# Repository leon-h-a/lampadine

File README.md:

### Connection between Arduino and PCB header
    ARD_13  -> 1
    ARD_12  -> 2
    ARD_11  -> 3
    ARD_10  -> 4
    ARD_GND -> 5

### Settings for programming via Arduino (platformio)
1. Install platformio on Windows
2. Init project ```pio project init --board attiny85``` ($ pio boards)
3. Install dependency ```pio lib install ADCTouch```
4. Setup Platformio to flash via Arduino (platformio.ini)

        [env:attiny85]
        platform = atmelavr
        board = attiny85
        framework = arduino
        upload_protocol = stk500v1
        lib_deps = martin2250/ADCTouch@^1.0.4
        upload_flags =
                -P$UPLOAD_PORT
                -b$UPLOAD_SPEED
        upload_port = COM7
        upload_speed = 19200

5. Flash with ```pio run --target upload```

### In case of avrdude verification error, mismatch byte

Remember to power PCB via USB-C before uploading.

### Timing issues

Define 'board_build.f_cpu' flag in platformio.ini conf file

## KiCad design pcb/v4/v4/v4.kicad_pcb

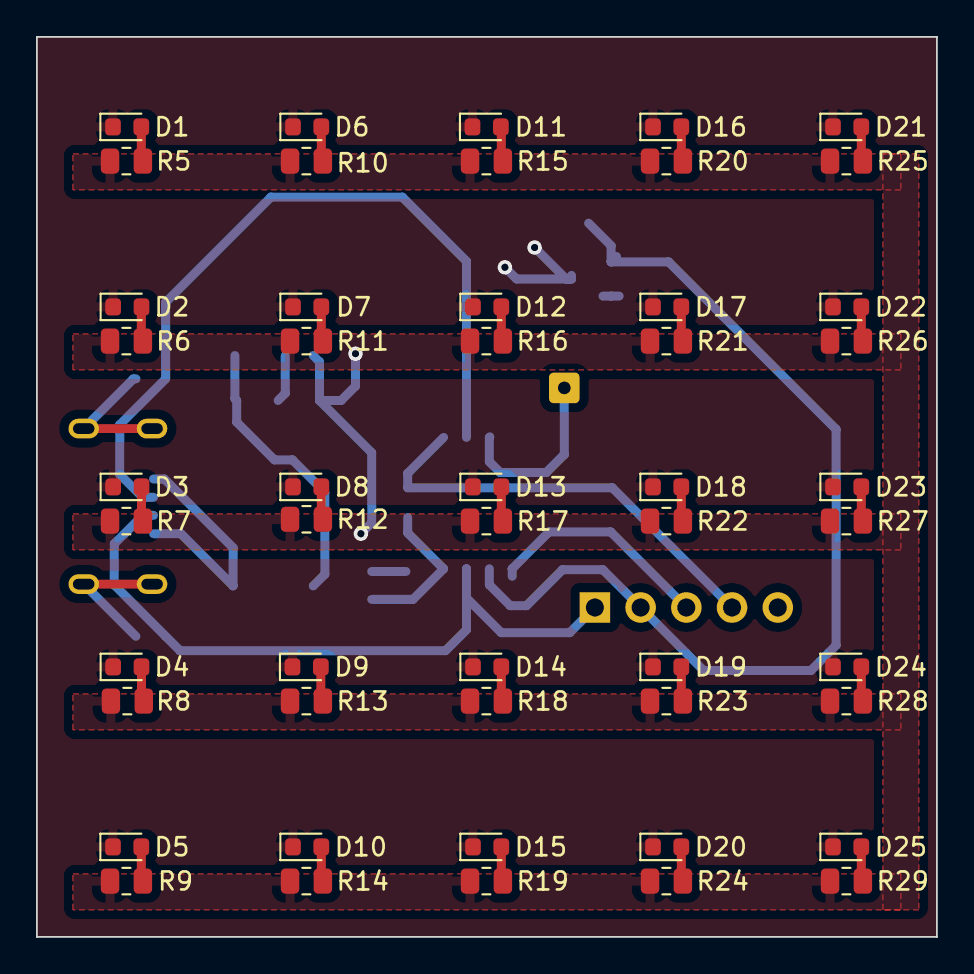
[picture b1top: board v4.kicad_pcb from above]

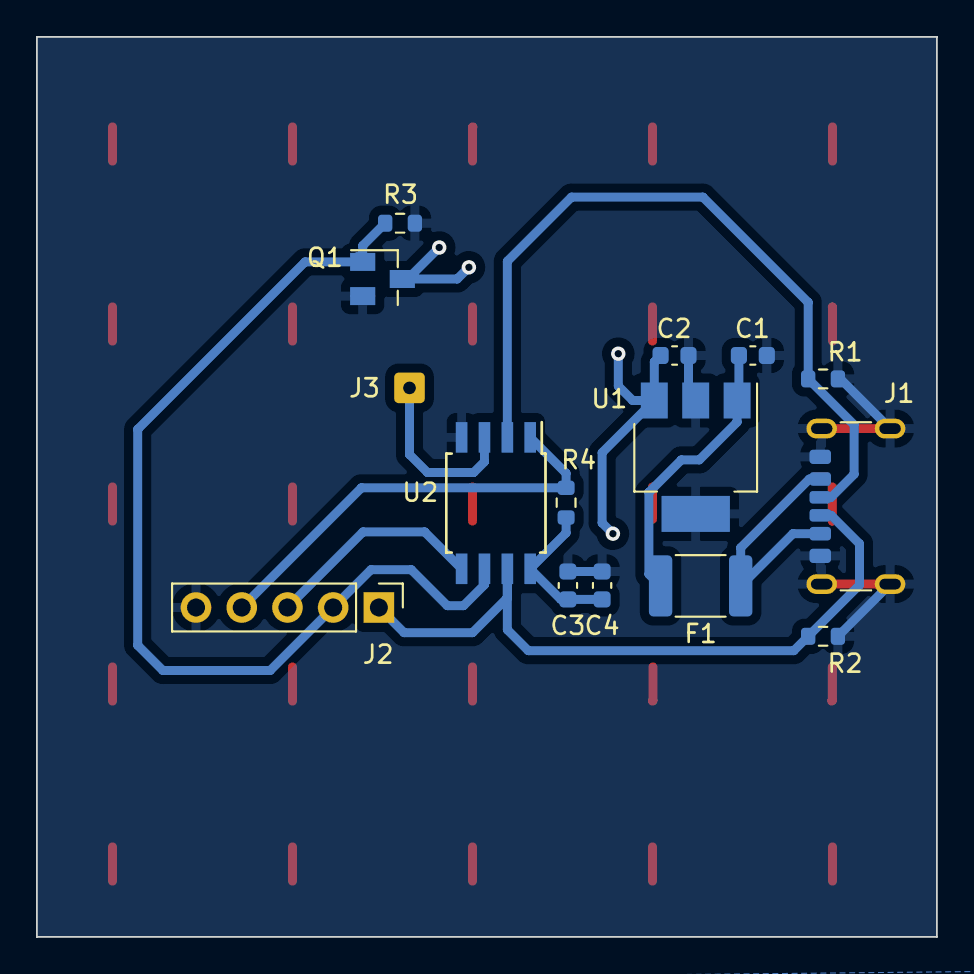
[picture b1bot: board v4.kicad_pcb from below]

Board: 2 copper layers, 50.0 x 50.0 mm, 65 parts (15 on the bottom side), 37 nets.

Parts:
C1, C2: 1uF; C_0603_1608Metric
C3: 0.1uF; C_0603_1608Metric
C4: 4.7uF; C_0603_1608Metric
D1, D2, D3, D4, D5, D6, D7, D8, D9, D10, D11, D12, D13, D14, D15, D16, D17, D18, D19, D20, D21, D22, D23, D24, D25: WHITE; D_0603_1608Metric
F1: Polyfuse; Fuse_1812_4532Metric_Pad1.30x3.40mm_HandSolder
J1: USB_C_Receptacle_PowerOnly_6P; USB_C_Receptacle_GCT_USB4125-xx-x-0190_6P_TopMnt_Horizontal
J2: Conn_01x05_Socket; PinHeader_1x05_P2.54mm_Vertical
J3: External Capacitance; SolderWire-0.15sqmm_1x01_D0.5mm_OD1.5mm
Q1: NMOS; SuperSOT-3
R1, R2: 5k1; R_0603_1608Metric
R3, R4: 10k; R_0603_1608Metric
R5, R6, R7, R8, R9, R10, R11, R12, R13, R14, R15, R16, R17, R18, R19, R20, R21, R22, R23, R24, R25, R26, R27, R28, R29: 500; R_0805_2012Metric
U1: MCP1703Ax-500xxDB; SOT-223-3_TabPin2
U2: ATtiny85-20S; SOIC-8W_5.3x5.3mm_P1.27mm

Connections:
CIRC_PWR: C2.1, R5.1, R6.1, R7.1, R8.1, R9.1, R10.1, R11.1, R12.1, R13.1, R14.1, R15.1, R16.1, R17.1, R18.1, R19.1, R20.1, R21.1, R22.1, R23.1, R24.1, R25.1, R26.1, R27.1, R28.1, R29.1, U1.3 (VO)
GND: C1.2, C2.2, C3.2, C4.2, J1.A12 (GND), J1.B12 (GND), J1.S1 (SHIELD), J2.5, Q1.2 (S), R1.2, R2.2, R3.2, U1.2 (GND), U2.4 (GND)
IC_PS: C3.1, C4.1, R4.2, U2.8 (VCC)
LED_CTRL: J2.2, Q1.1 (G), R3.1, U2.6 (PB1)
LED_OUT: D1.1 (K), D2.1 (K), D3.1 (K), D4.1 (K), D5.1 (K), D6.1 (K), D7.1 (K), D8.1 (K), D9.1 (K), D10.1 (K), D11.1 (K), D12.1 (K), D13.1 (K), D14.1 (K), D15.1 (K), D16.1 (K), D17.1 (K), D18.1 (K), D19.1 (K), D20.1 (K), D21.1 (K), D22.1 (K), D23.1 (K), D24.1 (K), D25.1 (K), Q1.3 (D)
unnamed: D1.2 (A), R5.2
unnamed: D2.2 (A), R6.2
unnamed: D3.2 (A), R7.2
unnamed: D4.2 (A), R8.2
unnamed: D5.2 (A), R9.2
unnamed: D6.2 (A), R10.2
unnamed: D7.2 (A), R11.2
unnamed: D8.2 (A), R12.2
unnamed: D9.2 (A), R13.2
unnamed: D10.2 (A), R14.2
unnamed: D11.2 (A), R15.2
unnamed: D12.2 (A), R16.2
unnamed: D13.2 (A), R17.2
unnamed: D14.2 (A), R18.2
unnamed: D15.2 (A), R19.2
unnamed: D16.2 (A), R20.2
unnamed: D17.2 (A), R21.2
unnamed: D18.2 (A), R22.2
unnamed: D19.2 (A), R23.2
unnamed: D20.2 (A), R24.2
unnamed: D21.2 (A), R25.2
unnamed: D22.2 (A), R26.2
unnamed: D23.2 (A), R27.2
unnamed: D24.2 (A), R28.2
unnamed: D25.2 (A), R29.2
unnamed: F1.1, J1.A9 (VBUS), J1.B9 (VBUS)
unnamed: J2.3, U2.5 (AREF/PB0)
unnamed: J2.4, R4.1, U2.1 (~RESET/PB5)
SRC_CAP1: J1.A5 (CC1), J2.1, R2.1, U2.7 (PB2)
SRC_CAP2: J1.B5 (CC2), R1.1, U2.2 (XTAL1/PB3)
TOUCH_SENS_EXT: J3.1, U2.3 (XTAL2/PB4)
USB_PWR: C1.1, F1.2, U1.1 (VI)

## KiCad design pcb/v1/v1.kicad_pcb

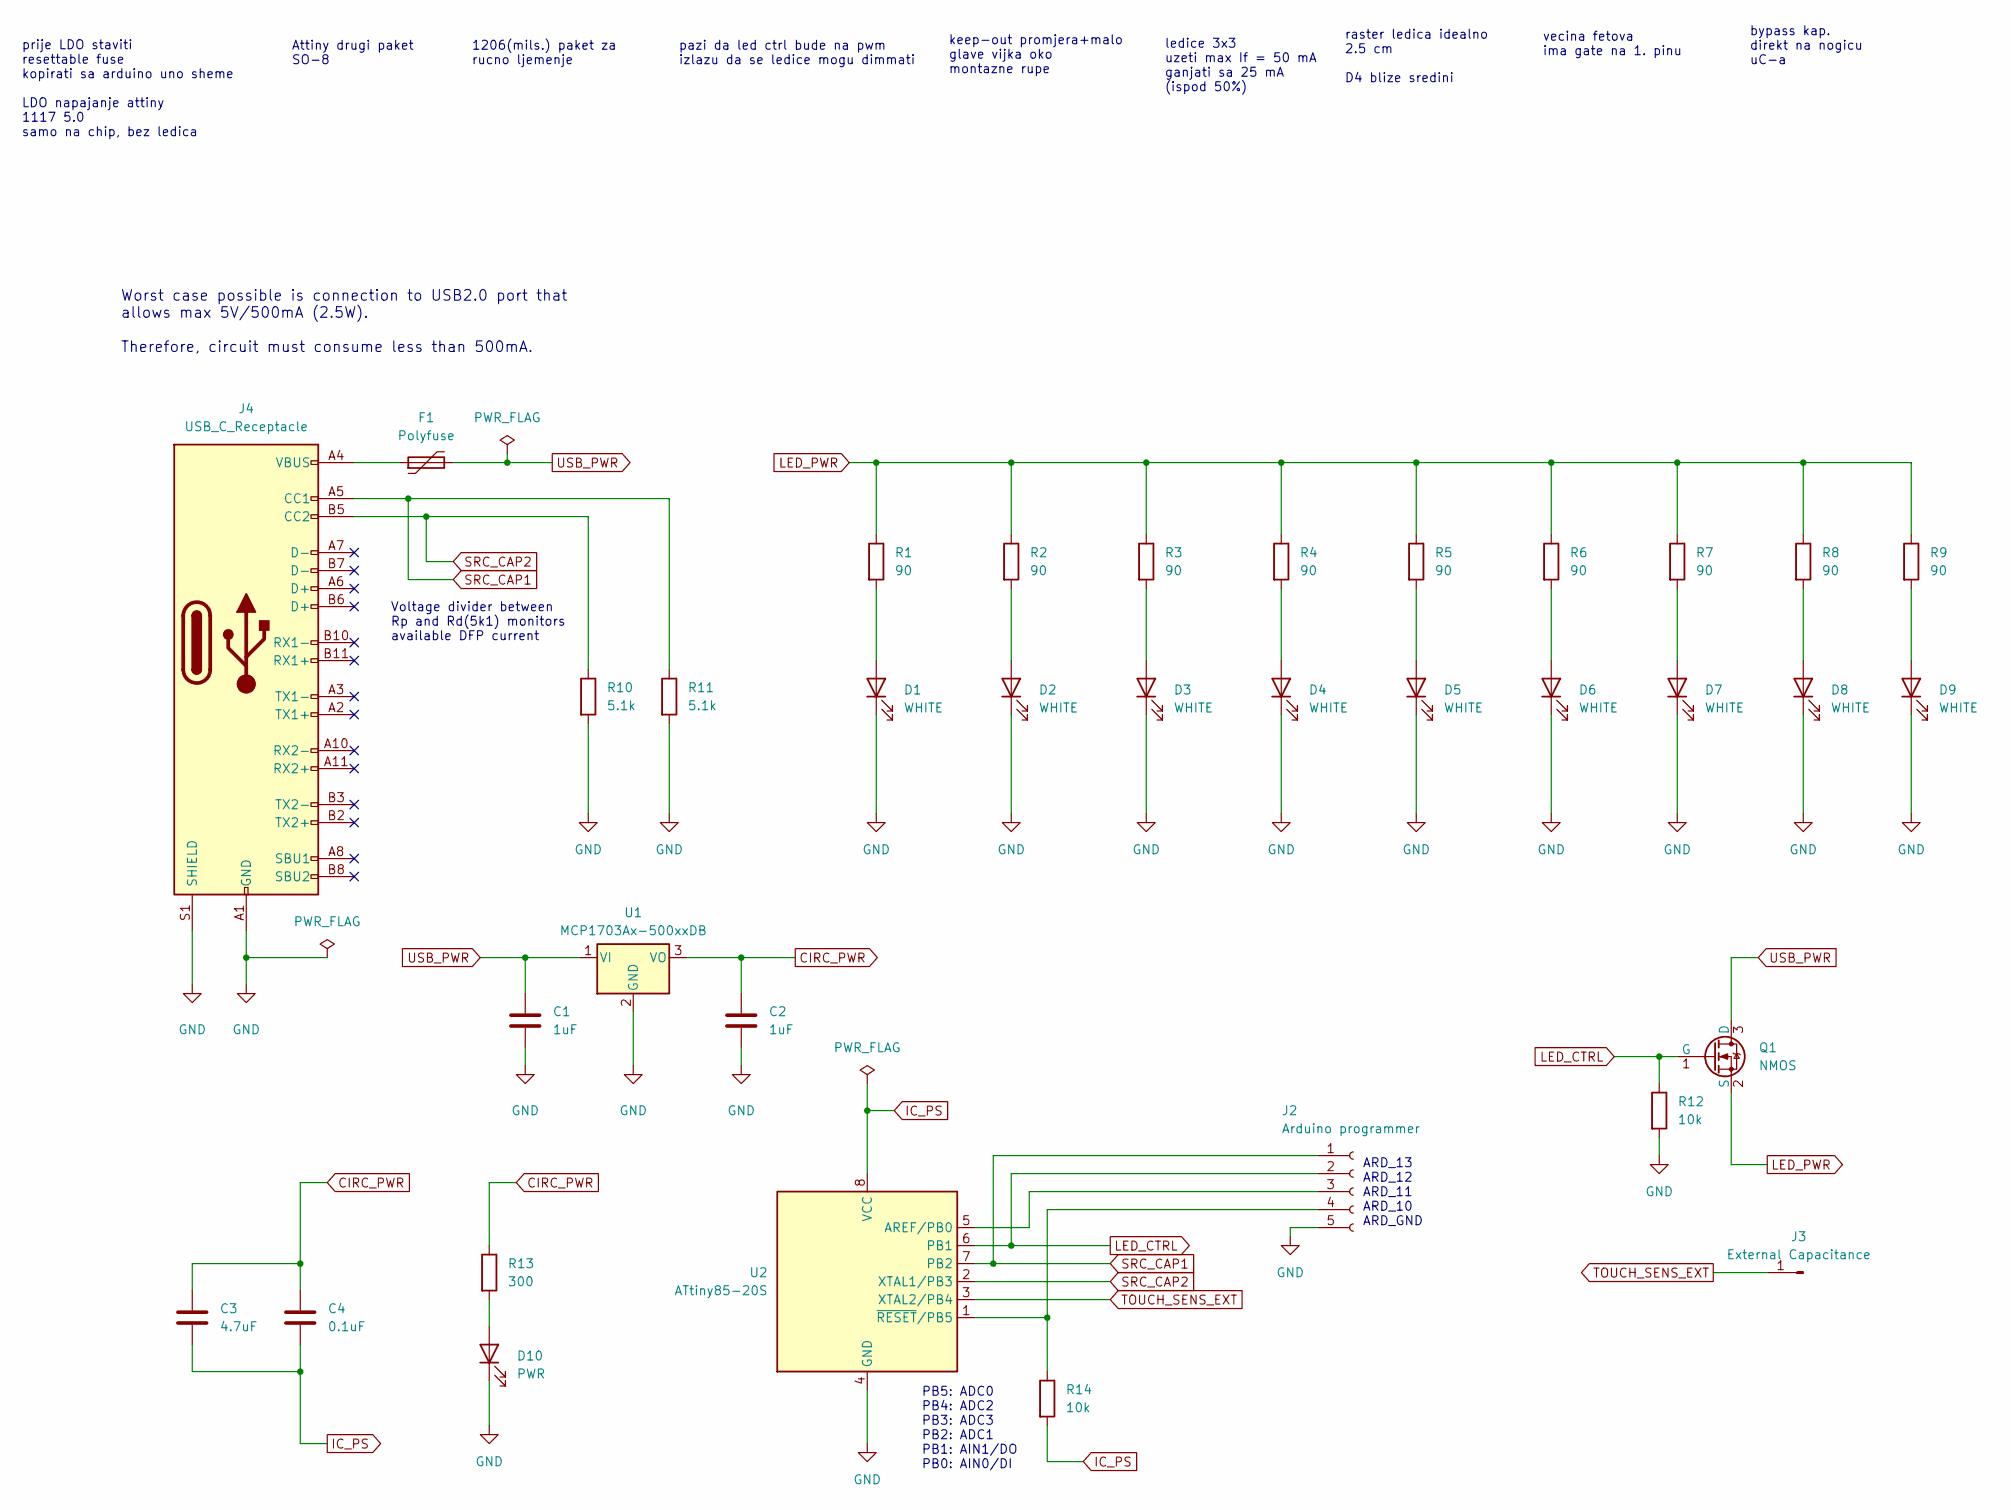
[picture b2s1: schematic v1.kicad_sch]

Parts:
C1, C2: 1uF; C_1206_3216Metric_Pad1.33x1.80mm_HandSolder
C3: 4.7uF; C_1206_3216Metric_Pad1.33x1.80mm_HandSolder
C4: 0.1uF; C_1206_3216Metric_Pad1.33x1.80mm_HandSolder
D1, D2, D3, D4, D5, D6, D7, D8, D9: WHITE; D_1206_3216Metric_Pad1.42x1.75mm_HandSolder
D10: PWR; D_0201_0603Metric_Pad0.64x0.40mm_HandSolder
F1: Polyfuse; Fuse_1812_4532Metric_Pad1.30x3.40mm_HandSolder
J2: Arduino programmer; PinHeader_1x05_P1.00mm_Horizontal
J3: External Capacitance; SolderWirePad_1x01_SMD_1x2mm
J4: USB_C_Receptacle; USB_C_Receptacle_Amphenol_12401610E4-2A
Q1: NMOS; SuperSOT-3
R1, R2, R3, R4, R5, R6, R7, R8, R9: 90; R_0603_1608Metric_Pad0.98x0.95mm_HandSolder
R10, R11: 5.1k; R_0603_1608Metric_Pad0.98x0.95mm_HandSolder
R12, R14: 10k; R_0603_1608Metric_Pad0.98x0.95mm_HandSolder
R13: 300; R_0603_1608Metric_Pad0.98x0.95mm_HandSolder
U1: MCP1703Ax-500xxDB; SOT-223-3_TabPin2
U2: ATtiny85-20S; SOIC-8W_5.3x5.3mm_P1.27mm

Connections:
CIRC_PWR: C2.1, C3.1, C4.1, R13.1, U1.3 (VO)
GND: C1.2, C2.2, D1.1 (K), D2.1 (K), D3.1 (K), D4.1 (K), D5.1 (K), D6.1 (K), D7.1 (K), D8.1 (K), D9.1 (K), D10.1 (K), J2.5, J4.A1 (GND), J4.A12 (GND), J4.B1 (GND), J4.B12 (GND), J4.S1 (SHIELD), R10.2, R11.2, R12.2, U1.2 (GND), U2.4 (GND)
IC_PS: C3.2, C4.2, R14.2, U2.8 (VCC)
LED_CTRL: J2.2, Q1.1 (G), R12.1, U2.6 (PB1)
LED_PWR: Q1.2 (S), R1.1, R2.1, R3.1, R4.1, R5.1, R6.1, R7.1, R8.1, R9.1
unnamed: D1.2 (A), R1.2
unnamed: D2.2 (A), R2.2
unnamed: D3.2 (A), R3.2
unnamed: D4.2 (A), R4.2
unnamed: D5.2 (A), R5.2
unnamed: D6.2 (A), R6.2
unnamed: D7.2 (A), R7.2
unnamed: D8.2 (A), R8.2
unnamed: D9.2 (A), R9.2
unnamed: D10.2 (A), R13.2
unnamed: F1.1, J4.A4 (VBUS), J4.A9 (VBUS), J4.B4 (VBUS), J4.B9 (VBUS)
unnamed: J2.3, U2.5 (AREF/PB0)
unnamed: J2.4, R14.1, U2.1 (~RESET/PB5)
SRC_CAP1: J2.1, J4.A5 (CC1), R11.1, U2.7 (PB2)
SRC_CAP2: J4.B5 (CC2), R10.1, U2.2 (XTAL1/PB3)
TOUCH_SENS_EXT: J3.1, U2.3 (XTAL2/PB4)
USB_PWR: C1.1, F1.2, Q1.3 (D), U1.1 (VI)

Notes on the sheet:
ARD_13 ARD_12 ARD_11 ARD_10 ARD_GND
ledice 3x3 uzeti max If = 50 mA ganjati sa 25 mA (ispod 50%)
vecina fetova ima gate na 1. pinu
pazi da led ctrl bude na pwm izlazu da se ledice mogu dimmati
raster ledica idealno 2.5 cm D4 blize sredini
bypass kap. direkt na nogicu uC-a
keep-out promjera+malo glave vijka oko montazne rupe
1206(mils.) paket za rucno ljemenje
Voltage divider between Rp and Rd(5k1) monitors available DFP current
PB5: ADC0 PB4: ADC2 PB3: ADC3 PB2: ADC1 PB1: AIN1/DO PB0: AIN0/DI
prije LDO staviti resettable fuse kopirati sa arduino uno sheme LDO napajanje attiny 1117 5.0 samo na chip, bez ledica
Worst case possible is connection to USB2.0 port that allows max 5V/500mA (2.5W). Therefore, circuit must consume less than 500mA.
Attiny drugi paket SO-8

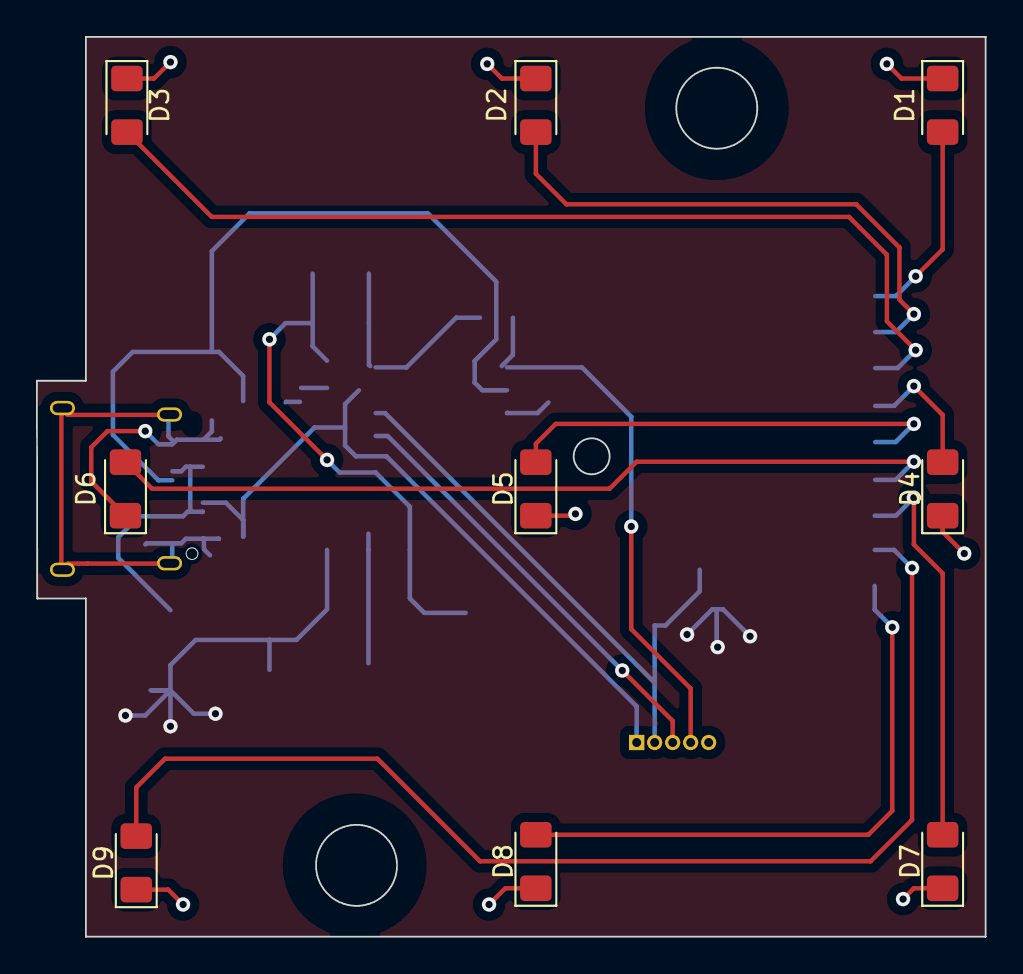
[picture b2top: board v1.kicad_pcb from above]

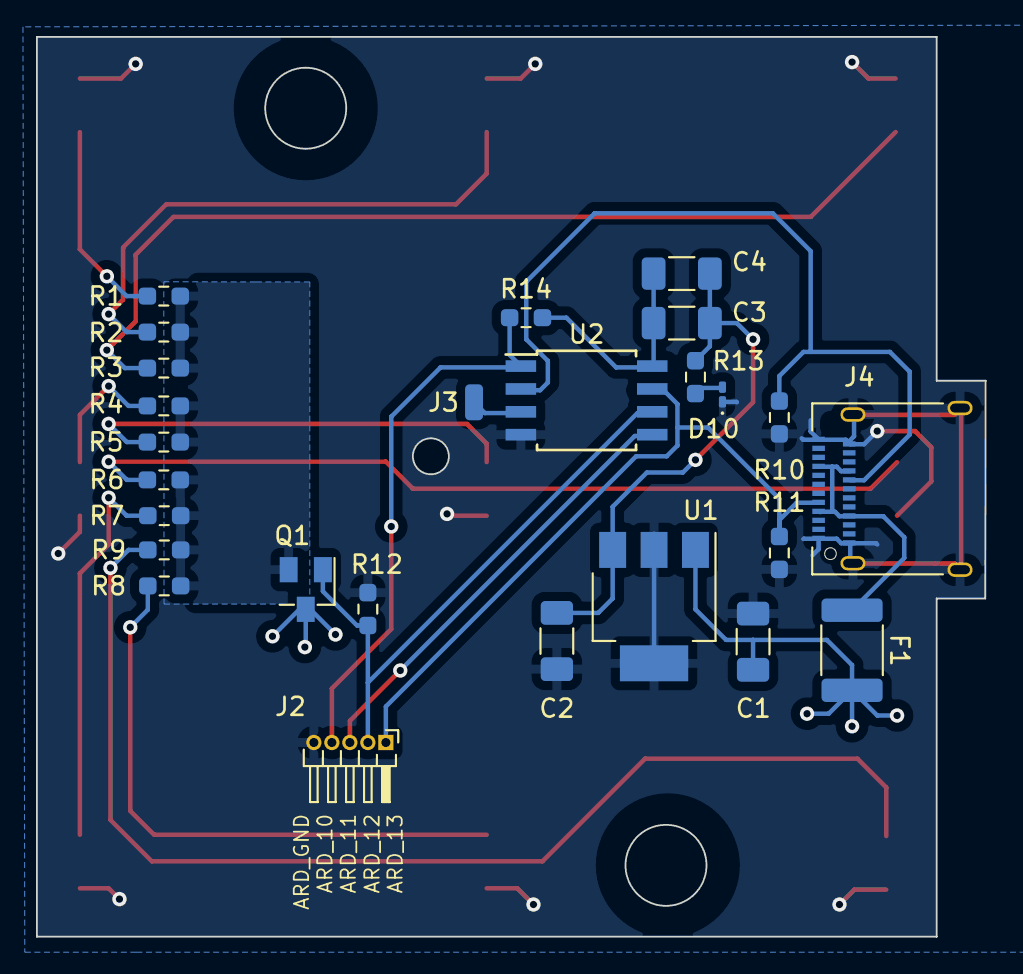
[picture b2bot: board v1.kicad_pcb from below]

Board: 2 copper layers, 52.7 x 50.0 mm, 35 parts (26 on the bottom side), 22 nets.

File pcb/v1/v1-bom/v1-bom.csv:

Number of boards;;;1;TOTAL;14.756;;;
Id;Designator;Footprint;Quantity;Designation;Price;Per board;Link;Comment
1;J2;PinHeader_1x05_P1.00mm_Horizontal;1;Arduino programmer;;;;.
2;D3,D9,D6,D2,D4,D5,D1,D8,D7;D_1206_3216Metric_Pad1.42x1.75mm_HandSolder;9;WHITE;0.725;6.525;https://hr.mouser.com/ProductDetail/ROHM-Semiconductor/CSL11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;.
3;Q1;SuperSOT-3;1;NMOS;0.595;0.595;https://hr.mouser.com/ProductDetail/onsemi-Fairchild/FDN5632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;.
4;C2,C1;C_1206_3216Metric_Pad1.33x1.80mm_HandSolder;2;1uF;0.791;1.582;https://hr.mouser.com/ProductDetail/KYOCERA-AVX/KAF31GR72A10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;.
5;R10,R11;R_0603_1608Metric_Pad0.98x0.95mm_HandSolder;2;5.1k;0.149;0.298;https://hr.mouser.com/ProductDetail/ROHM-Semiconductor/SDR03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;.
6;C4;C_1206_3216Metric_Pad1.33x1.80mm_HandSolder;1;0.1uF;0.093;0.093;https://hr.mouser.com/ProductDetail/Murata-Electronics/GCM03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;.
7;R3,R9,R6,R5,R2,R8,R1,R7,R4;R_0603_1608Metric_Pad0.98x0.95mm_HandSolder;9;90;0.093;0.837;https://hr.mouser.com/ProductDetail/ROHM-Semiconductor/SDR03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;.
8;U1;SOT-223-3_TabPin2;1;MCP1703Ax-500xxDB;0.772;0.772;https://hr.mouser.com/ProductDetail/Microchip-Technology/MCP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;.
9;F1;Fuse_1812_4532Metric_Pad1.30x3.40mm_HandSolder;1;Polyfuse;0.288;0.288;https://hr.mouser.com/ProductDetail/Bourns/MF-MSMF050-2?qs=t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;.
10;R12,R14;R_0603_1608Metric_Pad0.98x0.95mm_HandSolder;2;10k;0.121;0.242;https://hr.mouser.com/ProductDetail/ROHM-Semiconductor/ESR03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;.
11;J3;SolderWirePad_1x01_SMD_1x2mm;1;External Capacitance;;0;;.
12;D10;D_0201_0603Metric_Pad0.64x0.40mm_HandSolder;1;PWR;0.456;0.456;https://hr.mouser.com/ProductDetail/Lite-On/LTST-FC03AD-5A?q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;.
13;C3;C_1206_3216Metric_Pad1.33x1.80mm_HandSolder;1;4.7uF;0.205;0.205;https://hr.mouser.com/ProductDetail/Murata-Electronics/GRM03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;.
14;U2;SOIC-8W_5.3x5.3mm_P1.27mm;1;ATtiny85-20S;1.4;1.4;https://hr.mouser.com/ProductDetail/Microchip-Technology/ATT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;.
15;R13;R_0603_1608Metric_Pad0.98x0.95mm_HandSolder;1;300;0.093;0.093;https://hr.mouser.com/ProductDetail/YAGEO/RC0201FR-07300RL?q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;.
16;J4;USB_C_Receptacle_Amphenol_12401610E4-2A;1;USB_C_Receptacle;1.37;1.37;https://hr.mouser.com/ProductDetail/Amphenol-Commercial-Prod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;.

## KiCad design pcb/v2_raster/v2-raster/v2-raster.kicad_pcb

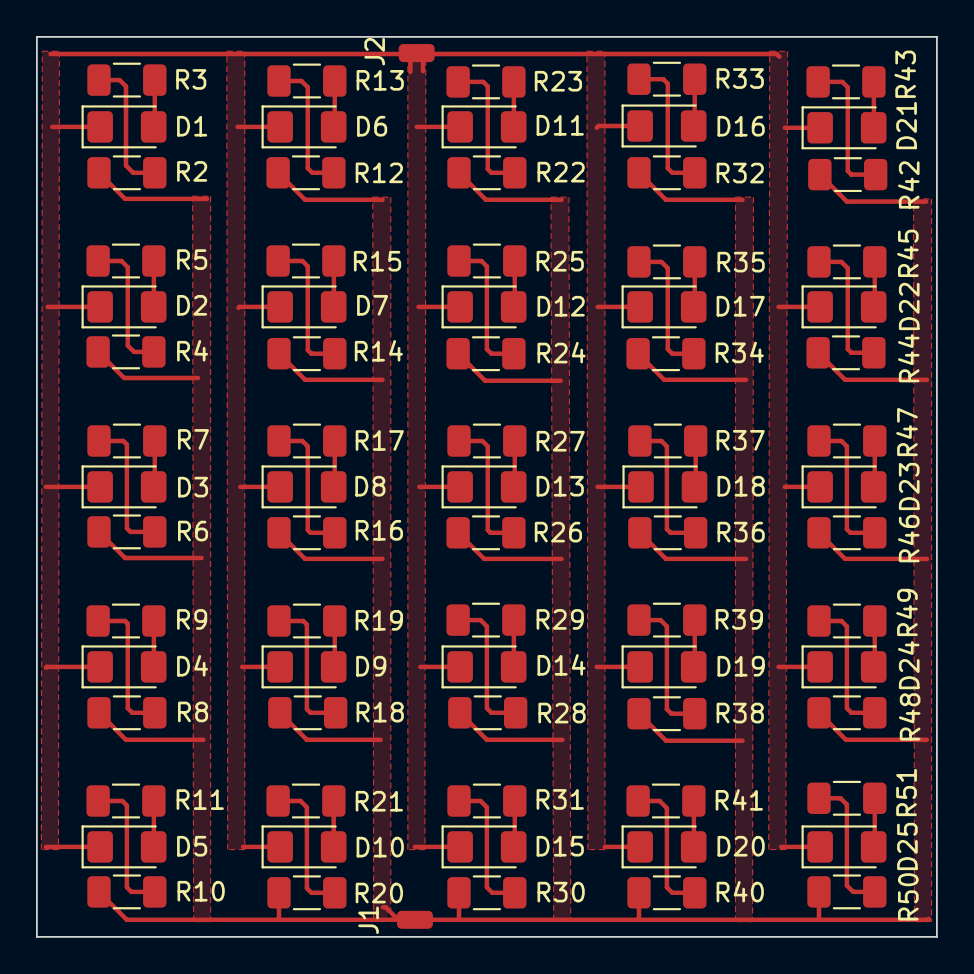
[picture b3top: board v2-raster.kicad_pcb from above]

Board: 2 copper layers, 50.0 x 50.0 mm, 77 parts (0 on the bottom side), 52 nets.

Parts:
D1, D2, D3, D4, D5, D6, D7, D8, D9, D10, D11, D12, D13, D14, D15, D16, D17, D18, D19, D20, D21, D22, D23, D24, D25: LED; D_1206_3216Metric_Pad1.42x1.75mm_HandSolder
J1, J2: Conn_01x01_Pin; SolderWirePad_1x01_SMD_1x2mm
R2, R4, R6, R8, R10, R12, R14, R16, R18, R20, R22, R24, R26, R28, R30, R32, R34, R36, R38, R40, R42, R44, R46, R48, R50: 0; R_1206_3216Metric_Pad1.30x1.75mm_HandSolder
R3, R5, R7, R9, R11, R13, R15, R17, R19, R21, R23, R25, R27, R29, R31, R33, R35, R37, R39, R41, R43, R45, R47, R49, R51: 500; R_1206_3216Metric_Pad1.30x1.75mm_HandSolder

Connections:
+5V: J1.1, R2.1, R4.1, R6.1, R8.1, R10.1, R12.1, R14.1, R16.1, R18.1, R20.1, R22.1, R24.1, R26.1, R28.1, R30.1, R32.1, R34.1, R36.1, R38.1, R40.1, R42.1, R44.1, R46.1, R48.1, R50.1
GND: D1.1 (K), D2.1 (K), D3.1 (K), D4.1 (K), D5.1 (K), D6.1 (K), D7.1 (K), D8.1 (K), D9.1 (K), D10.1 (K), D11.1 (K), D12.1 (K), D13.1 (K), D14.1 (K), D15.1 (K), D16.1 (K), D17.1 (K), D18.1 (K), D19.1 (K), D20.1 (K), D21.1 (K), D22.1 (K), D23.1 (K), D24.1 (K), D25.1 (K), J2.1
unnamed: D1.2 (A), R3.2
unnamed: D2.2 (A), R5.2
unnamed: D3.2 (A), R7.2
unnamed: D4.2 (A), R9.2
unnamed: D5.2 (A), R11.2
unnamed: D6.2 (A), R13.2
unnamed: D7.2 (A), R15.2
unnamed: D8.2 (A), R17.2
unnamed: D9.2 (A), R19.2
unnamed: D10.2 (A), R21.2
unnamed: D11.2 (A), R23.2
unnamed: D12.2 (A), R25.2
unnamed: D13.2 (A), R27.2
unnamed: D14.2 (A), R29.2
unnamed: D15.2 (A), R31.2
unnamed: D16.2 (A), R33.2
unnamed: D17.2 (A), R35.2
unnamed: D18.2 (A), R37.2
unnamed: D19.2 (A), R39.2
unnamed: D20.2 (A), R41.2
unnamed: D21.2 (A), R43.2
unnamed: D22.2 (A), R45.2
unnamed: D23.2 (A), R47.2
unnamed: D24.2 (A), R49.2
unnamed: D25.2 (A), R51.2
unnamed: R2.2, R3.1
unnamed: R4.2, R5.1
unnamed: R6.2, R7.1
unnamed: R8.2, R9.1
unnamed: R10.2, R11.1
unnamed: R12.2, R13.1
unnamed: R14.2, R15.1
unnamed: R16.2, R17.1
unnamed: R18.2, R19.1
unnamed: R20.2, R21.1
unnamed: R22.2, R23.1
unnamed: R24.2, R25.1
unnamed: R26.2, R27.1
unnamed: R28.2, R29.1
unnamed: R30.2, R31.1
unnamed: R32.2, R33.1
unnamed: R34.2, R35.1
unnamed: R36.2, R37.1
unnamed: R38.2, R39.1
unnamed: R40.2, R41.1
unnamed: R42.2, R43.1
unnamed: R44.2, R45.1
unnamed: R46.2, R47.1
unnamed: R48.2, R49.1
unnamed: R50.2, R51.1

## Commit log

2023-11-27 feat(main): hello world example
2023-11-27 feat(readme): added connection and programming explanation
2023-11-27 style(readme): updated
2023-11-27 feat(main): analog out ramp-up/down
2023-11-28 feat(cap touch): single ADC, working on Arduino
2023-11-28 feat(attiny85): cap input/DO LED working
2023-11-28 feat(attiny85): on/off and ramp-up/down working
2023-12-23 feat(pcb): added V1 files with revision notes for V2
2024-04-12 feat(code): add platformio setup
2024-04-12 refactor: project structure
2024-04-12 fix(pcb): files from OD
2024-04-12 feat(pcb): add v4
    * LEDs moved from Source to Drain branch of MOSFET
    * Bypass capacitors on Attiny series to parallel connection
2024-04-12 feat(code): attiny FW update via Arduino Uno
2024-04-12 docs: update flash instructions and pinout notes
2024-04-12 feat(code): add original from project restruct
2024-04-21 temp: backup
2024-06-24 feat(v4): basic blink working
2024-06-26 feat(v4): ADC in and LED out working
